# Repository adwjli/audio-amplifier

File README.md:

# Audio Amplifier

## Introduction
This is a Class D audio amplifier built around a TPA3122D2N amplifier from Texas Instrument. It features two stereo audio jacks that allows two sources to be connected to the amplifier at the same time (for example a music player and a laptop).

A slide switch allows selection of switch input source to feed into the amplifier. The onboard potentiometer provides volume control. Power is provided using a 16V DC 2A adapter. This audio amplifier was designed as part of a custom audio-visual setup.

The amplifier accepts an input voltage between 15V to 25V. The output power is 10W per channel. It can drive speakers with impedances between 4 and 8 Ohms.

## Gallery

## Copper Layers

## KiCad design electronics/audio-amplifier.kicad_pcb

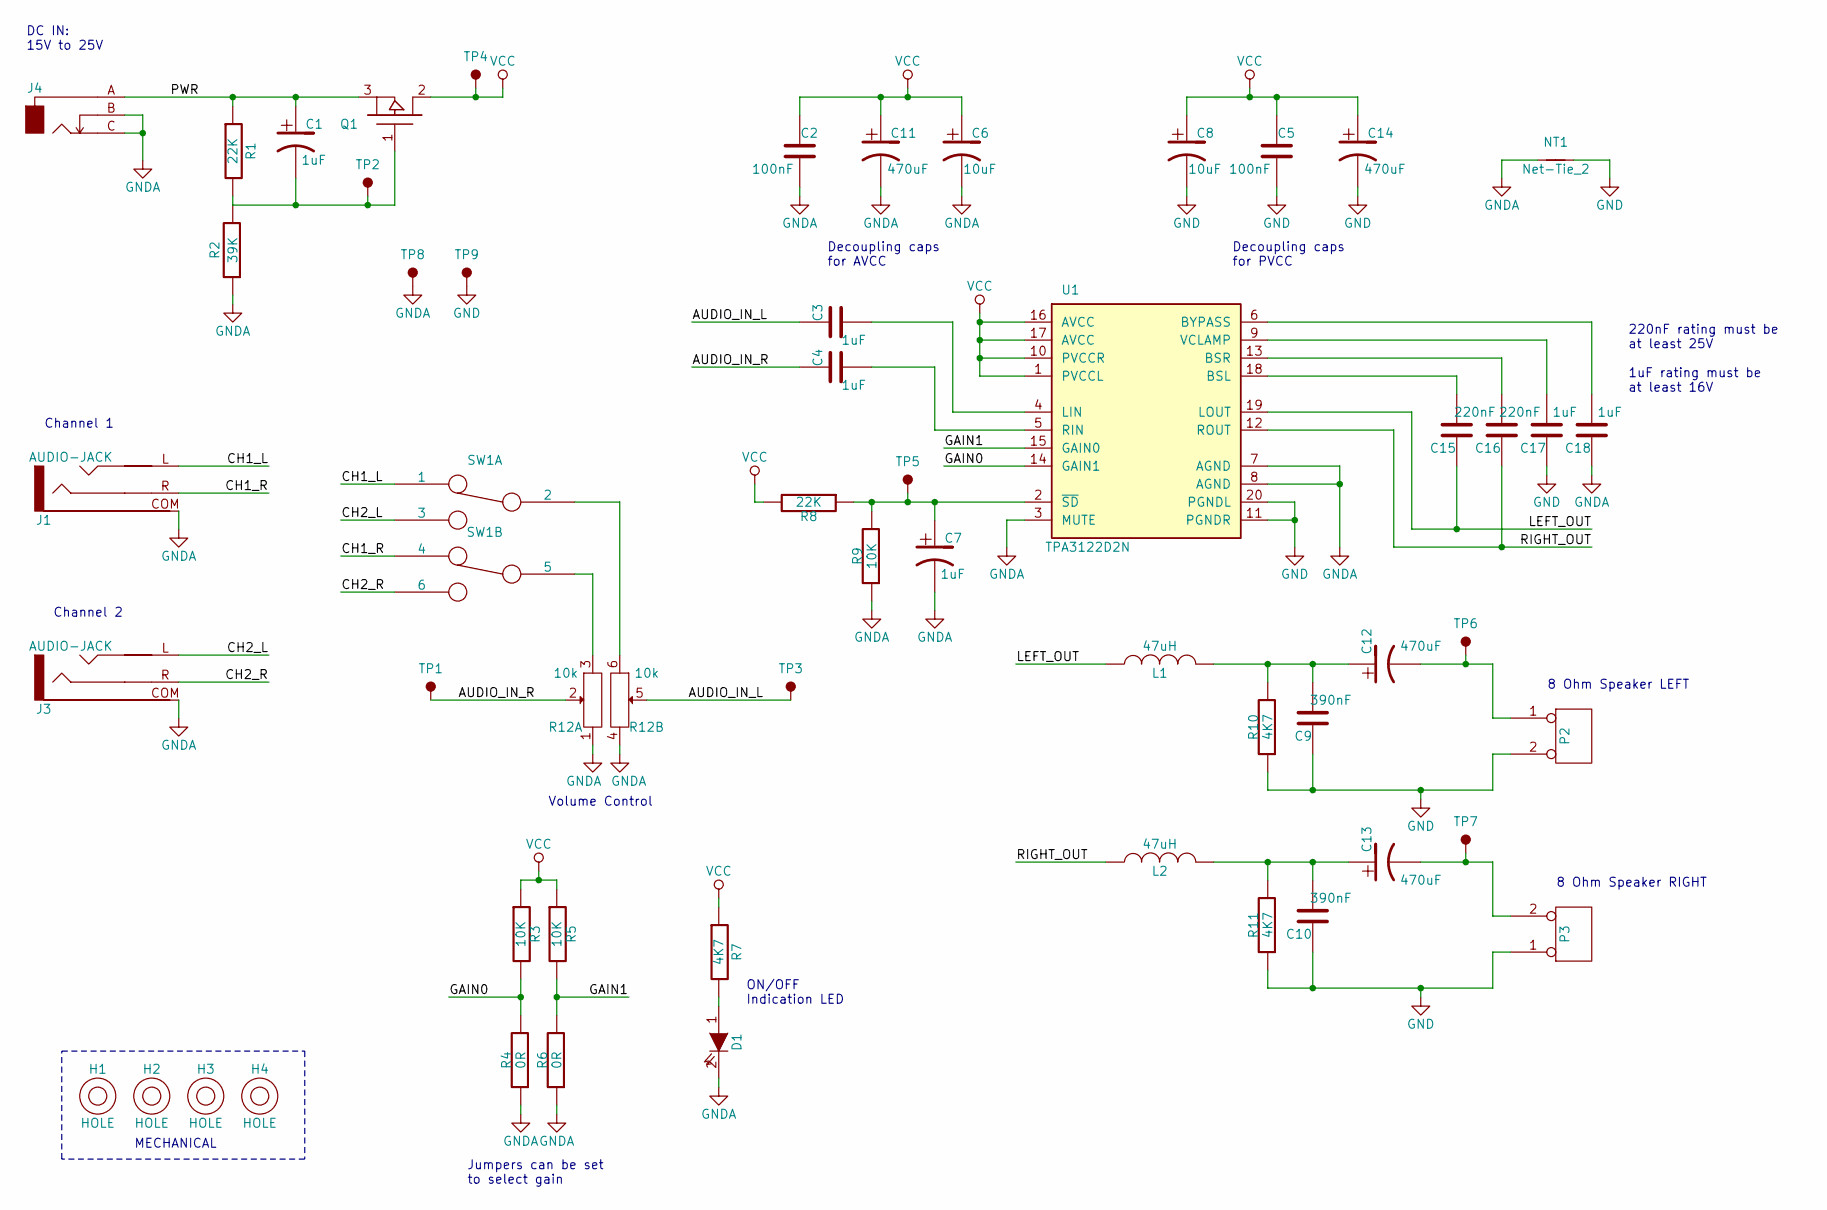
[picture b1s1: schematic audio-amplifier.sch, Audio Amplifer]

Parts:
C1, C6, C7, C8: CAP-POL-GENERIC; CAP-POL-GENERIC-TH-D4MM-P1.5MM
C2, C3, C4, C5, C9, C10, C15, C16, C17, C18: CAP-GENERIC; CAP-GENERIC-TH; Part Description Generic Through Hole Capacitor
C11, C12, C13, C14: CAP-POL-GENERIC; CAP-POL-GENERIC-TH-D8MM-P3.5MM
D1: LED-GENERIC-TH; Part Description Generic Through Hole LED
H1, H2, H3, H4: HOLE; HOLE_3.5MM
J1, J3: AUDIO-JACK
J4: ECS00108; Manufacturer Part Number 448-376
L1, L2: INDUCTOR-GENERIC; INDUCTOR-GENERIC-TH-D9.0MM-P5.0MM
NT1: Net-Tie_2; NetTie-2_THT_Pad1.0mm
P2, P3: HEADER-GENERIC-2WAY; HEADER-2-TH-P5.0MM
Q1: ECS00110; ECTO-220; Manufacturer Part Number AUIRF9Z34N
R1, R2, R3, R4, R5, R6, R7, R8, R9, R10, R11: RES-GENERIC; RES-GENERIC-TH; Part Description Generic Through Hole Resistor
R12: ECS00238; ECS00238F; Manufacturer Part Number 3310H-025-103L
SW1: ECS00237; ECS00237F; Manufacturer Part Number JS202011CQN
TP1, TP2, TP3, TP4, TP5, TP6, TP7, TP8, TP9: TP-2MM
U1: ECS00104; DIP-20; Manufacturer Part Number TPA3122D2N

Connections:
/AUDIO_IN_L: C3.1, R12.5, TP3.1
/AUDIO_IN_R: C4.1, R12.2, TP1.1
/CH1_L: J1.L, SW1.1
/CH1_R: J1.R, SW1.4
/CH2_L: J3.L, SW1.3
/CH2_R: J3.R, SW1.6
/GAIN0: R3.2, R4.2, U1.14 (GAIN1)
/GAIN1: R5.2, R6.2, U1.15 (GAIN0)
/LEFT_OUT: C15.1, L1.1, U1.19 (LOUT)
/PWR: C1.1, J4.A, Q1.3 (S), R1.1
/RIGHT_OUT: C16.1, L2.1, U1.12 (ROUT)
GND: C5.2, C8.2, C9.1, C10.1, C14.2, C17.1, NT1.2, P2.2 (PM), P3.1, R10.1, R11.1, TP9.1, U1.11 (PGNDR), U1.20 (PGNDL)
GNDA: C2.2, C6.2, C7.2, C11.2, C18.1, D1.2 (K), J1.COM, J3.COM, J4.B, J4.C, NT1.1, R2.1, R4.1, R6.1, R9.1, R12.1, R12.4, TP8.1, U1.3 (MUTE), U1.7 (AGND), U1.8 (AGND)
unnamed: C1.2, Q1.1 (G), R1.2, R2.2, TP2.1
unnamed: C3.2, U1.4 (LIN)
unnamed: C4.2, U1.5 (RIN)
unnamed: C7.1, R8.1, R9.2, TP5.1, U1.2 (~SD)
unnamed: C10.2, C13.1, L2.2, R11.2
unnamed: C9.2, C12.1, L1.2, R10.2
unnamed: C12.2, P2.1, TP6.1
unnamed: C13.2, P3.2 (PM), TP7.1
unnamed: C15.2, U1.18 (BSL)
unnamed: C16.2, U1.13 (BSR)
unnamed: C17.2, U1.9 (VCLAMP)
unnamed: C18.2, U1.6 (BYPASS)
unnamed: D1.1 (A), R7.2
unnamed: R12.3, SW1.5
unnamed: R12.6, SW1.2
VCC: C2.1, C5.1, C6.1, C8.1, C11.1, C14.1, Q1.2 (D), R3.1, R5.1, R7.1, R8.2, TP4.1, U1.1 (PVCCL), U1.10 (PVCCR), U1.16 (AVCC), U1.17 (AVCC)

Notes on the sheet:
ON/OFF Indication LED
Jumpers can be set to select gain
8 Ohm Speaker LEFT
8 Ohm Speaker RIGHT
220nF rating must be at least 25V 1uF rating must be at least 16V
Decoupling caps for PVCC
MECHANICAL
DC IN: 15V to 25V
Channel 1
Channel 2
Volume Control
Decoupling caps for AVCC

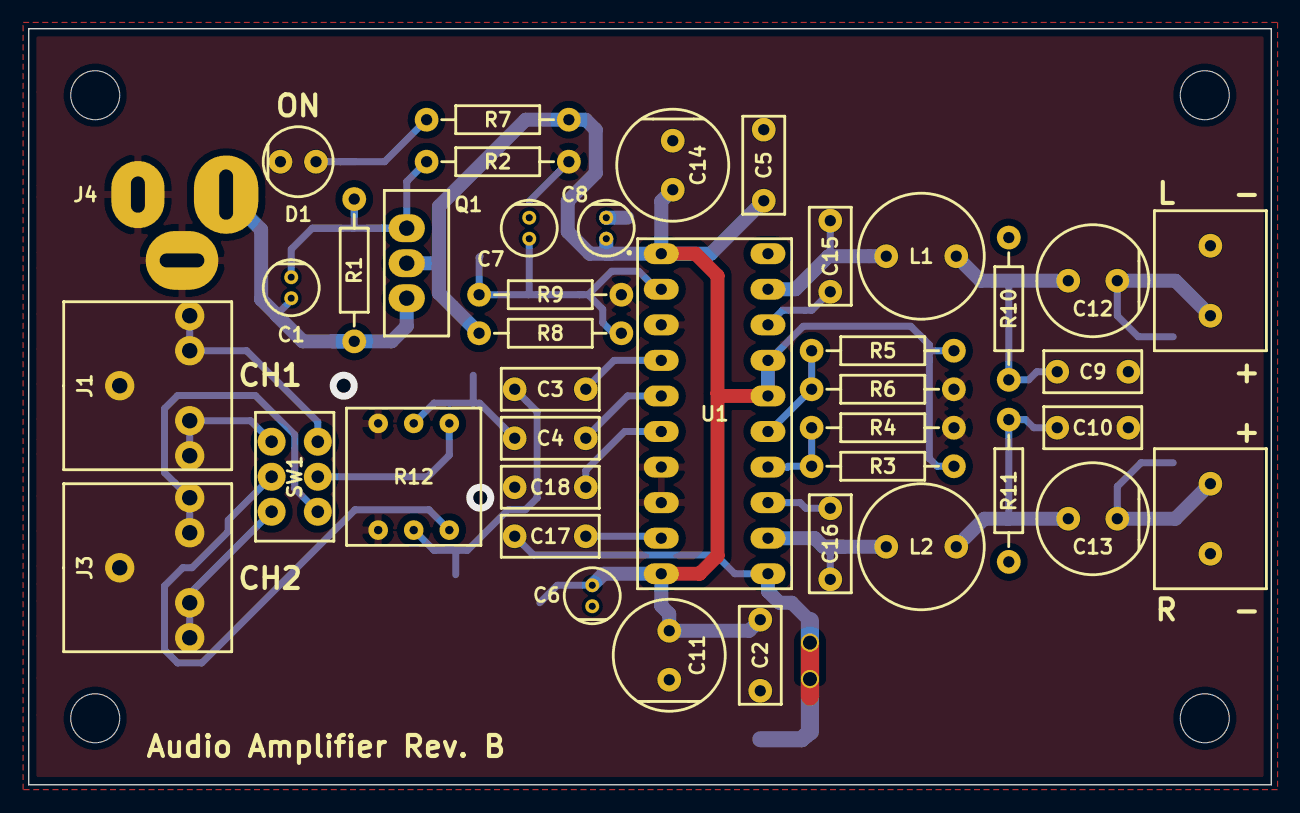
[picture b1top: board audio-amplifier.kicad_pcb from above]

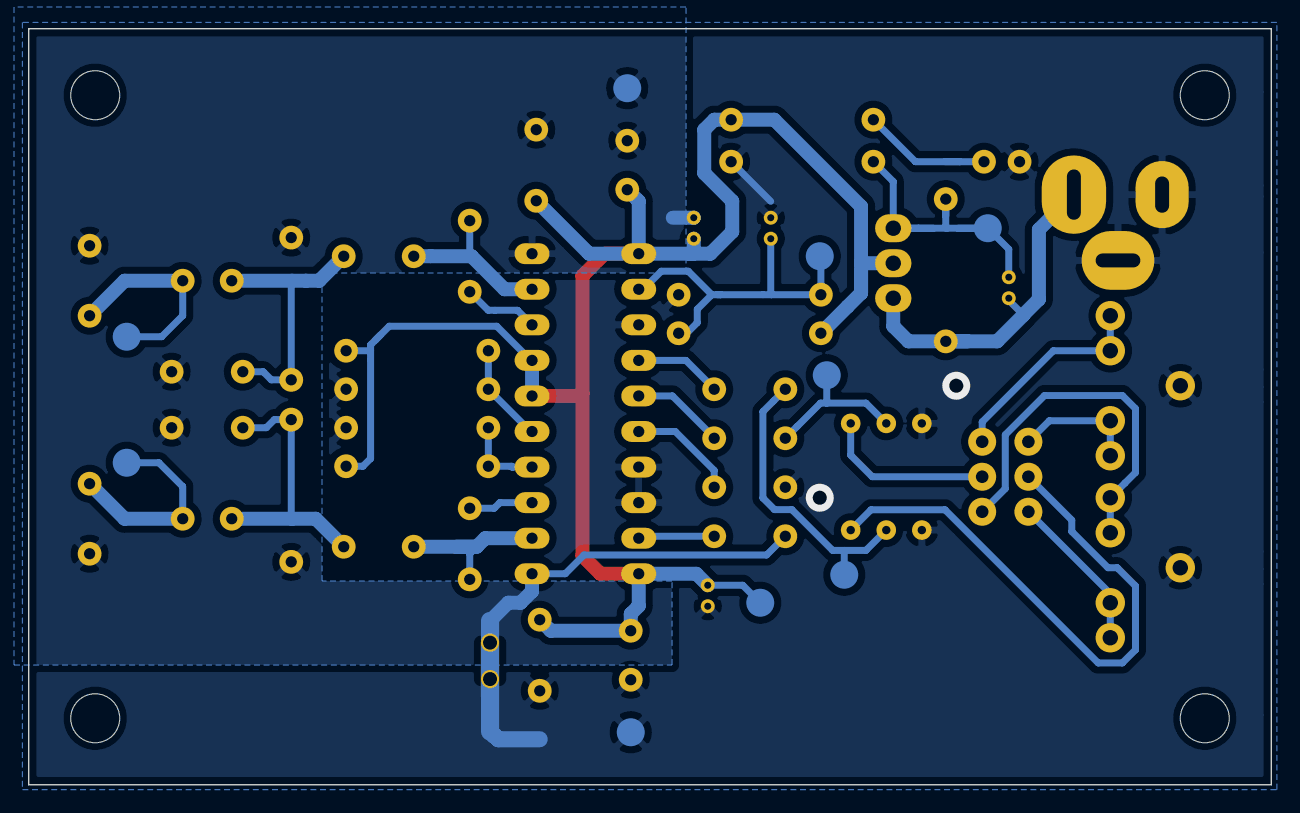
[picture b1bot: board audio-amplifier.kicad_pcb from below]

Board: 2 copper layers, 88.8 x 54.0 mm, 55 parts (9 on the bottom side), 29 nets.

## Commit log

2020-05-15 Update README.md
    Update the title of this file
2020-05-15 First commit.
2020-05-15 Removing unnecessary files that were acciedentally commited.
2020-05-15 Adding the modified .gitignore file.
2020-05-20 Uploading completed design files.
2020-05-22 Adding drawings and updates to README files.
2020-05-22 Uploading more images, and updates to README.md.
2020-05-22 Updating README.md.
